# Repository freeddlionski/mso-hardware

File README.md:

# МСО74 — железо

Плата контроллера, корпус поста и документация отладочной платы. Прошивка — `mso-firmware`, сервер — `mso-server`,
ферма — `mso-farm`. Сюда можно давать доступ разводчикам и конструкторам без доступа к коду.

| Папка | Что там |
|---|---|
| `plata/` | своя плата контроллера: ТЗ для разработчиков (`TZ_razrabotchiku.md`) и рабочий черновик (`TZ.md`), дальше — схема, разводка, Gerber и BOM по ревизиям (`rev_A/`, `rev_B/`…) |
| `korpus/` | корпус поста: эскизы модулей, чертежи и файлы резки (`chertezhi/modul_tablo/` — модуль табло, в работе) |
| `a147/` | документация отладочной платы A147 (стенд): схемы производителя |

Как подключается периферия к контроллеру и что делает прошивка (MDB, монетник) — `mso-firmware/docs/MDB.md`.

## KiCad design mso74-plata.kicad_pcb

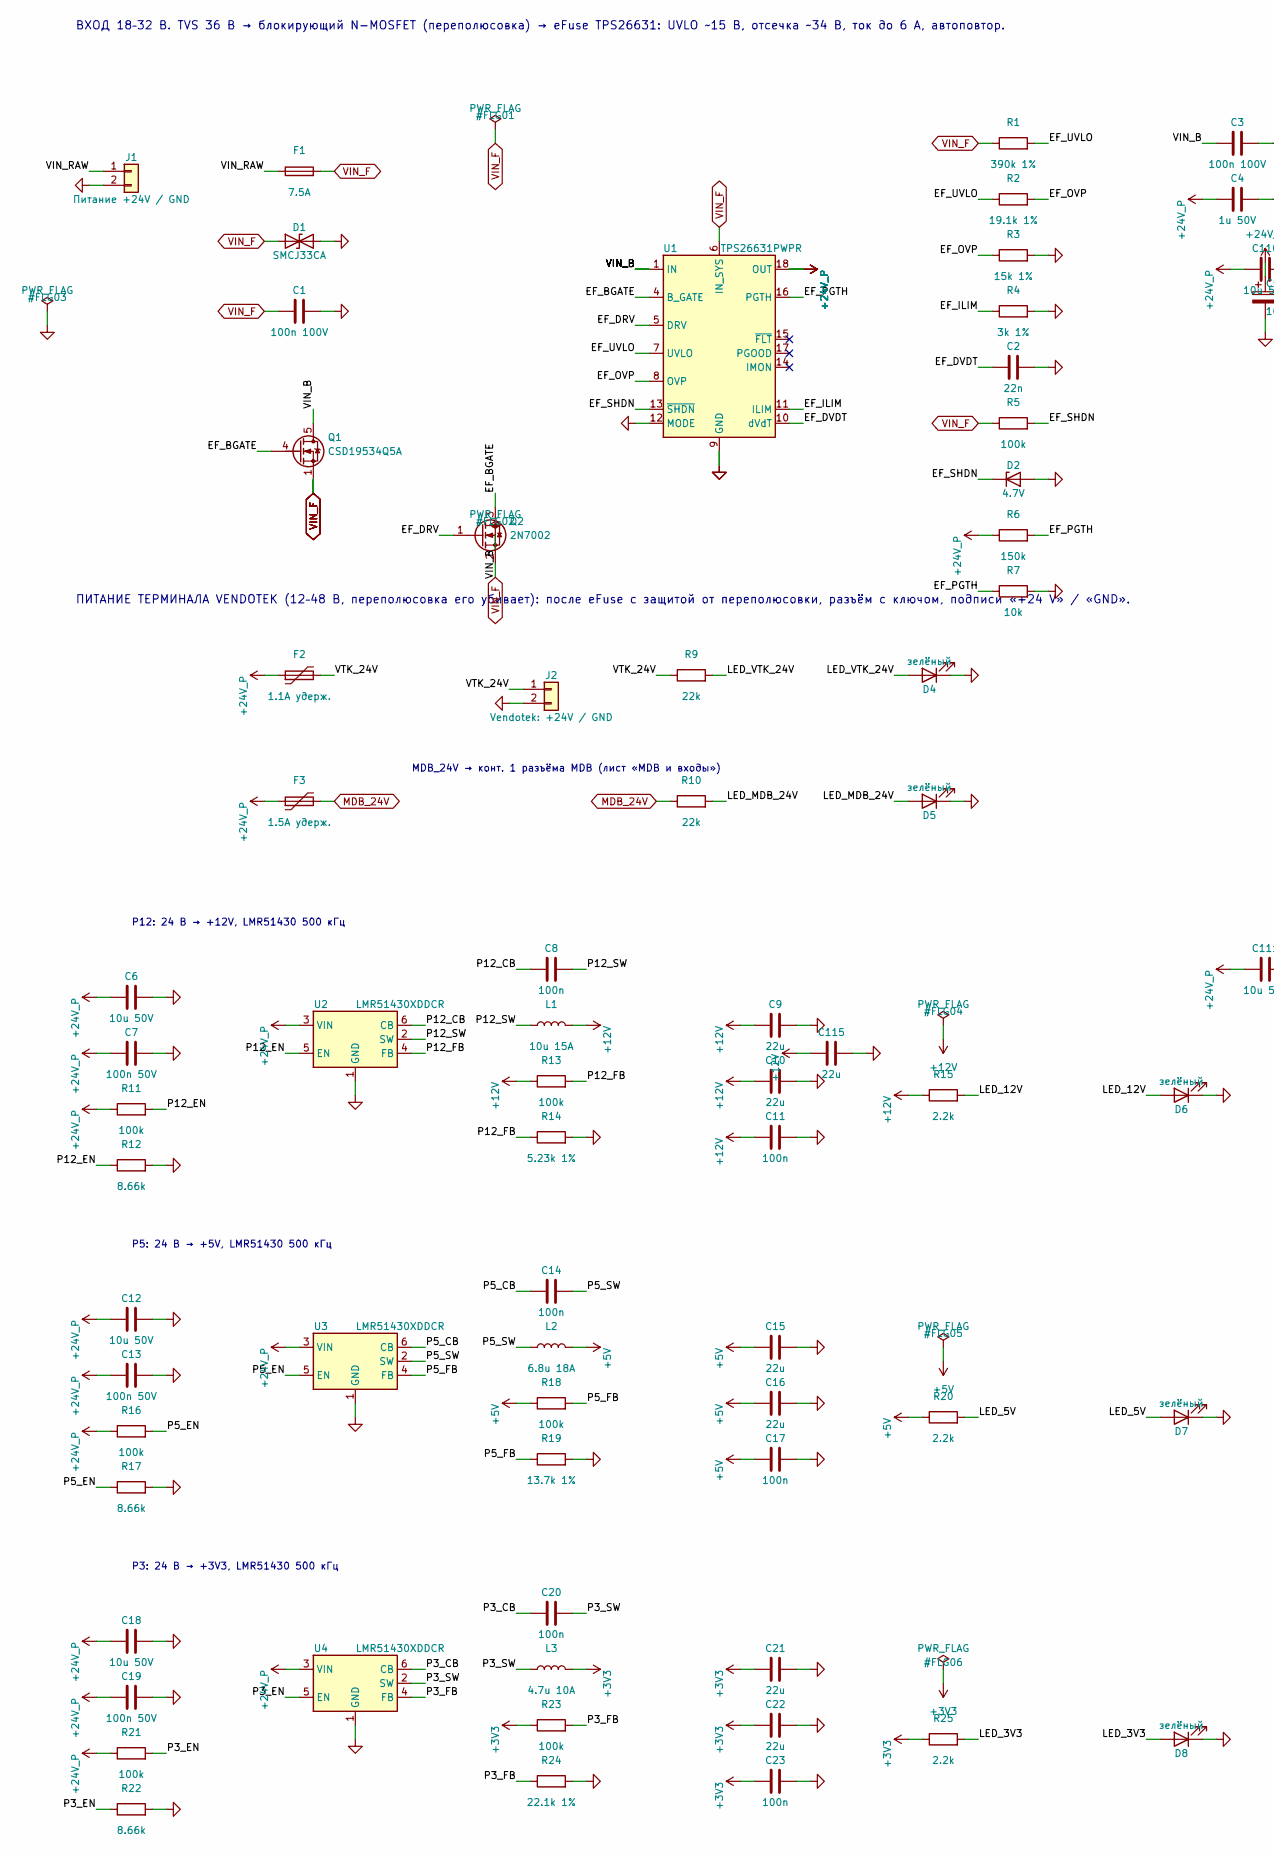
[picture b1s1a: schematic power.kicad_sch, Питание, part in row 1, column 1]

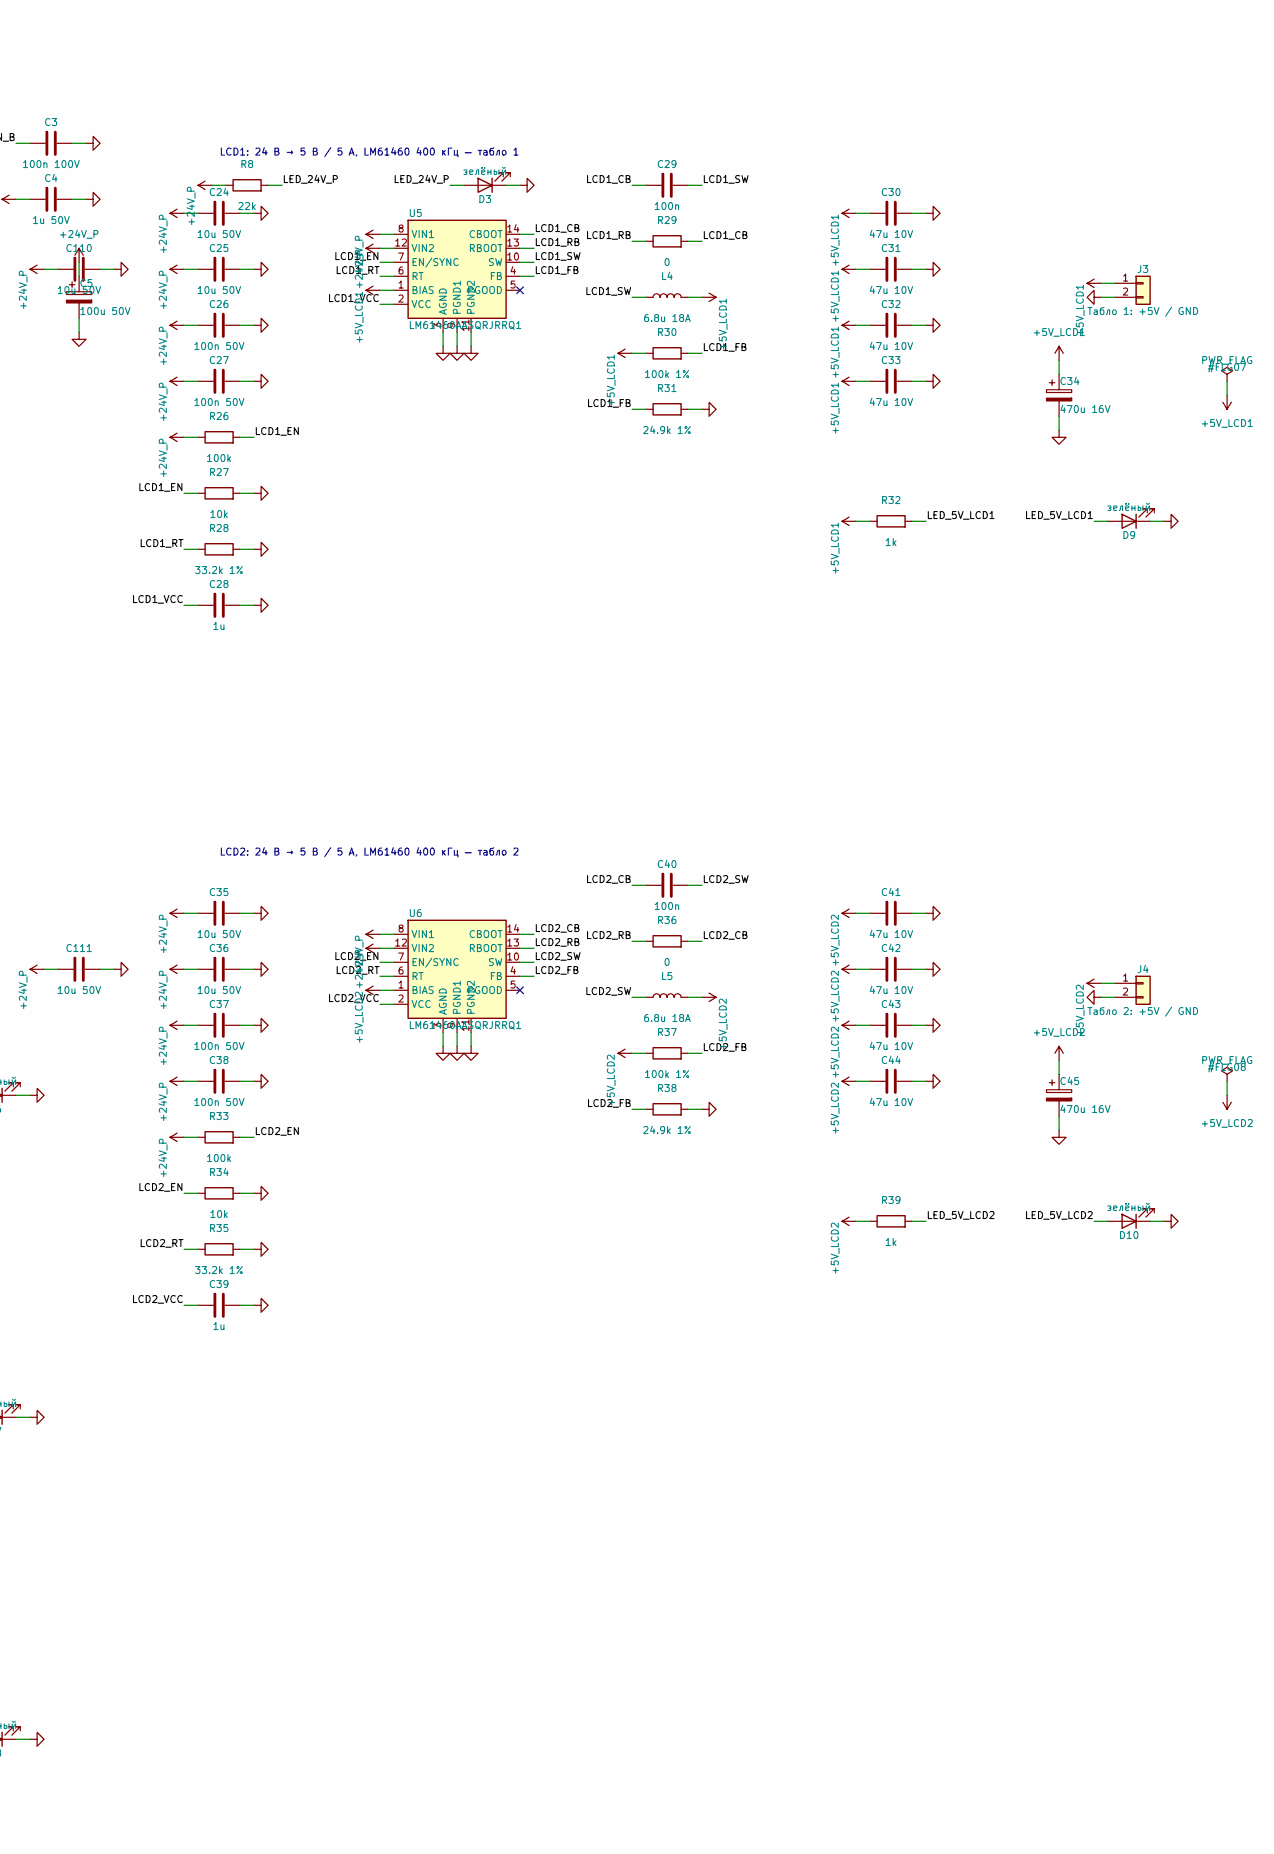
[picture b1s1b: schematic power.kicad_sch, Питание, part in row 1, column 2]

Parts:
C1, C3: 100n 100V; C_0603_1608Metric; MPN CL10B104KC8NNNC; LCSC C15725
C2: 22n; C_0603_1608Metric; MPN CC0603JRX7R9BB223; LCSC C277528
C4: 1u 50V; C_1206_3216Metric; MPN CL31B105KBHNNNE; LCSC C1848
C5: 100u 50V; CP_Elec_10x10.5; MPN MAL214699103E3; LCSC C5158069
C6, C12, C18, C24, C25, C35, C36, C110, C111: 10u 50V; C_1210_3225Metric; MPN GRM32ER71H106KA12L; LCSC C77102
C7, C13, C19, C26, C27, C37, C38: 100n 50V; C_0603_1608Metric; MPN CC0603KRX7R9BB104; LCSC C14663
C8, C11, C14, C17, C20, C23, C29, C40: 100n; C_0603_1608Metric; MPN CC0603KRX7R9BB104; LCSC C14663
C9, C10, C115: 22u; C_1210_3225Metric; MPN CL32A226KAJNNNE; LCSC C52306
C15, C16, C21, C22: 22u; C_1206_3216Metric; MPN CL31A226KOHNNNE; LCSC C90146
C28, C39: 1u; C_0603_1608Metric; MPN 0603X105K500NT; LCSC C157684
C30, C31, C32, C33, C41, C42, C43, C44: 47u 10V; C_1210_3225Metric; MPN C3225X5R1A476MT000E; LCSC C76680
C34, C45: 470u 16V; CP_Elec_10x10.5; MPN 25TLV470M10X10.5; LCSC C2905295
D1: SMCJ33CA; D_SMC; MPN SMCJ33CA; LCSC C224050
D2: 4.7V; D_SOD-123; MPN MMSZ4688; LCSC C22395547
D3, D4, D5, D6, D7, D8, D9, D10: зелёный; LED_0603_1608Metric; MPN KT-0603YG; LCSC C2289
F1: 7.5A; Fuseholder_Blade_Mini_Keystone_3568; MPN 3568-10; LCSC C3205378
F2: 1.1A удерж.; Fuse_2920_7451Metric; MPN 2920L110/60MR; LCSC C315903
F3: 1.5A удерж.; Fuse_2920_7451Metric; MPN SMD2920-150/60N; LCSC C6165178
J1: Питание +24V / GND; KANGNEX_WJ2EDGRC_1x02_P5.08mm_Drill1.7; MPN WJ2EDGRC-5.08-02P-14-00A; LCSC C3697
J2: Vendotek: +24V / GND; KANGNEX_WJ2EDGRC_1x02_P5.08mm_Drill1.7; MPN WJ2EDGRC-5.08-02P-14-00A; LCSC C3697
J3: Табло 1: +5V / GND; TerminalBlock_Phoenix_MKDS-1,5-2-5.08_1x02_P5.08mm_Horizont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; MPN WJ500V-5.08-2P; LCSC C8465
J4: Табло 2: +5V / GND; TerminalBlock_Phoenix_MKDS-1,5-2-5.08_1x02_P5.08mm_Horizont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; MPN WJ500V-5.08-2P; LCSC C8465
L1: 10u 15A; L_Bourns_SRP1245A; MPN SRP1265A-100M; LCSC C840531
L2, L4, L5: 6.8u 18A; L_Bourns_SRP1245A; MPN SRP1265A-6R8M; LCSC C2041326
L3: 4.7u 10A; L_Bourns_SRP7028A_7.3x6.6mm; MPN SRP7028A-4R7M; LCSC C840529
Q1: CSD19534Q5A; Texas_DQJ_VSONP-8_5x6mm_CSD19534Q5A; MPN CSD19534Q5A; LCSC C114200
Q2: 2N7002; SOT-23; MPN 2N7002-7-F (Diodes Inc.); LCSC C85049
R1: 390k 1%; R_0603_1608Metric; MPN 0603WAF3903T5E; LCSC C23150
R2: 19.1k 1%; R_0603_1608Metric; MPN 0603WAF1912T5E; LCSC C22897
R3: 15k 1%; R_0603_1608Metric; MPN 0603WAF1502T5E; LCSC C22809
R4: 3k 1%; R_0603_1608Metric; MPN 0603WAF3001T5E; LCSC C4211
R5, R11, R13, R16, R18, R21, R23, R26, R33: 100k; R_0603_1608Metric; MPN 0603WAF1003T5E; LCSC C25803
R6: 150k; R_0603_1608Metric; MPN 0603WAF1503T5E; LCSC C22807
R7, R27, R34: 10k; R_0603_1608Metric; MPN 0603WAF1002T5E; LCSC C25804
R8, R9, R10: 22k; R_0603_1608Metric; MPN 0603WAF2202T5E; LCSC C31850
R12, R17, R22: 8.66k; R_0603_1608Metric; MPN 0603WAF8661T5E; LCSC C23114
R14: 5.23k 1%; R_0603_1608Metric; MPN 0603WAF5231T5E; LCSC C23068
R15, R20, R25: 2.2k; R_0603_1608Metric; MPN 0603WAF2201T5E; LCSC C4190
R19: 13.7k 1%; R_0603_1608Metric; MPN 0603WAF1372T5E; LCSC C22793
R24: 22.1k 1%; R_0603_1608Metric; MPN FRC0603F2212TS; LCSC C2960862
R28, R35: 33.2k 1%; R_0603_1608Metric; MPN RC0603FR-0733K2L; LCSC C185338
R29, R36: 0; R_0603_1608Metric; MPN 0603WAF0000T5E; LCSC C21189
R30, R37: 100k 1%; R_0603_1608Metric; MPN 0603WAF1003T5E; LCSC C25803
R31, R38: 24.9k 1%; R_0603_1608Metric; MPN RC0603FR-0724K9L; LCSC C137761
R32, R39: 1k; R_0603_1608Metric; MPN 0603WAF1001T5E; LCSC C21190
U1: TPS26631PWPR; HTSSOP-20-1EP_4.4x6.5mm_P0.65mm_EP3.4x6.5mm_Mask2.96x2.96mm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; MPN TPS26631PWPR; LCSC C2866319
U2, U3, U4: LMR51430XDDCR; SOT-23-6; MPN LMR51430XDDCR; LCSC C5185863
U5, U6: LM61460AASQRJRRQ1; Texas_RJR_VQFN-HR-14_3.5x4mm; MPN LM61460AASQRJRRQ1; LCSC C1855832

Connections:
+3V3: C21.1, C22.1, C23.1, L3.2, R23.1, R25.1; also elsewhere on the board
+5V: C15.1, C16.1, C17.1, L2.2, R18.1, R20.1; also elsewhere on the board
+5V_LCD1: C30.1, C31.1, C32.1, C33.1, C34.1, J3.1, L4.2, R30.1, R32.1, U5.1 (BIAS); also elsewhere on the board
+5V_LCD2: C41.1, C42.1, C43.1, C44.1, C45.1, J4.1, L5.2, R37.1, R39.1, U6.1 (BIAS); also elsewhere on the board
+12V: C9.1, C10.1, C11.1, C115.1, L1.2, R13.1, R15.1; also elsewhere on the board
+24V_P: C4.1, C5.1, C6.1, C7.1, C12.1, C13.1, C18.1, C19.1, C24.1, C25.1, C26.1, C27.1, C35.1, C36.1, C37.1, C38.1, C110.1, C111.1, F2.1, F3.1, R6.1, R8.1, R11.1, R16.1, R21.1, R26.1, R33.1, U1.18 (OUT), U1.19 (OUT), U1.20 (OUT), U2.3 (VIN), U3.3 (VIN), U4.3 (VIN), U5.8 (VIN1), U5.12 (VIN2), U6.8 (VIN1), U6.12 (VIN2); also elsewhere on the board
/Питание/EF_BGATE: Q1.4 (G), Q2.3 (D), U1.4 (B_GATE)
/Питание/EF_DRV: Q2.1 (G), U1.5 (DRV)
/Питание/EF_DVDT: C2.1, U1.10 (dVdT)
/Питание/EF_ILIM: R4.1, U1.11 (ILIM)
/Питание/EF_OVP: R2.2, R3.1, U1.8 (OVP)
/Питание/EF_PGTH: R6.2, R7.1, U1.16 (PGTH)
/Питание/EF_SHDN: D2.1 (K), R5.2, U1.13 (~SHDN)
/Питание/EF_UVLO: R1.2, R2.1, U1.7 (UVLO)
/Питание/LCD1_CB: C29.1, R29.2, U5.14 (CBOOT)
/Питание/LCD1_EN: R26.2, R27.1, U5.7 (EN/SYNC)
/Питание/LCD1_FB: R30.2, R31.1, U5.4 (FB)
/Питание/LCD1_RB: R29.1, U5.13 (RBOOT)
/Питание/LCD1_RT: R28.1, U5.6 (RT)
/Питание/LCD1_SW: C29.2, L4.1, U5.10 (SW)
/Питание/LCD1_VCC: C28.1, U5.2 (VCC)
/Питание/LCD2_CB: C40.1, R36.2, U6.14 (CBOOT)
/Питание/LCD2_EN: R33.2, R34.1, U6.7 (EN/SYNC)
/Питание/LCD2_FB: R37.2, R38.1, U6.4 (FB)
/Питание/LCD2_RB: R36.1, U6.13 (RBOOT)
/Питание/LCD2_RT: R35.1, U6.6 (RT)
/Питание/LCD2_SW: C40.2, L5.1, U6.10 (SW)
/Питание/LCD2_VCC: C39.1, U6.2 (VCC)
/Питание/LED_3V3: D8.2 (A), R25.2
/Питание/LED_5V: D7.2 (A), R20.2
/Питание/LED_5V_LCD1: D9.2 (A), R32.2
/Питание/LED_5V_LCD2: D10.2 (A), R39.2
/Питание/LED_12V: D6.2 (A), R15.2
/Питание/LED_24V_P: D3.2 (A), R8.2
/Питание/LED_MDB_24V: D5.2 (A), R10.2
/Питание/LED_VTK_24V: D4.2 (A), R9.2
/Питание/P3_CB: C20.1, U4.6 (CB)
/Питание/P3_EN: R21.2, R22.1, U4.5 (EN)
/Питание/P3_FB: R23.2, R24.1, U4.4 (FB)
/Питание/P3_SW: C20.2, L3.1, U4.2 (SW)
/Питание/P5_CB: C14.1, U3.6 (CB)
/Питание/P5_EN: R16.2, R17.1, U3.5 (EN)
/Питание/P5_FB: R18.2, R19.1, U3.4 (FB)
/Питание/P5_SW: C14.2, L2.1, U3.2 (SW)
/Питание/P12_CB: C8.1, U2.6 (CB)
/Питание/P12_EN: R11.2, R12.1, U2.5 (EN)
/Питание/P12_FB: R13.2, R14.1, U2.4 (FB)
/Питание/P12_SW: C8.2, L1.1, U2.2 (SW)
/Питание/VIN_B: C3.1, Q1.5 (D), U1.1 (IN), U1.2 (IN), U1.3 (IN)
/Питание/VIN_RAW: F1.1, J1.1
/Питание/VTK_24V: F2.2, J2.1, R9.1
GND: C1.2, C2.2, C3.2, C4.2, C5.2, C6.2, C7.2, C9.2, C10.2, C11.2, C12.2, C13.2, C15.2, C16.2, C17.2, C18.2, C19.2, C21.2, C22.2, C23.2, C24.2, C25.2, C26.2, C27.2, C28.2, C30.2, C31.2, C32.2, C33.2, C34.2, C35.2, C36.2, C37.2, C38.2, C39.2, C41.2, C42.2, C43.2, C44.2, C45.2, C110.2, C111.2, C115.2, D1.2 (A2), D2.2 (A), D3.1 (K), D4.1 (K), D5.1 (K), D6.1 (K), D7.1 (K), D8.1 (K), D9.1 (K), D10.1 (K), J1.2, J2.2, J3.2, J4.2, R3.2, R4.2, R7.2, R12.2, R14.2, R17.2, R19.2, R22.2, R24.2, R27.2, R28.2, R31.2, R34.2, R35.2, R38.2, U1.9 (GND), U1.12 (MODE), U1.21 (GND), U2.1 (GND), U3.1 (GND), U4.1 (GND), U5.3 (AGND), U5.9 (PGND1), U5.11 (PGND2), U6.3 (AGND), U6.9 (PGND1), U6.11 (PGND2); also elsewhere on the board
MDB_24V: F3.2, R10.1; also elsewhere on the board
VIN_F: C1.1, D1.1 (A1), F1.2, Q1.1 (S), Q1.2 (S), Q1.3 (S), Q2.2 (S), R1.1, R5.1, U1.6 (IN_SYS); also elsewhere on the board

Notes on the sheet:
ВХОД 18–32 В. TVS 36 В → блокирующий N-MOSFET (переполюсовка) → eFuse TPS26631: UVLO ~15 В, отсечка ~34 В, ток до 6 А, автоповтор.
ПИТАНИЕ ТЕРМИНАЛА VENDOTEK (12–48 В, переполюсовка его убивает): после eFuse с защитой от переполюсовки, разъём с ключом, подписи «+24 V» / «GND».
MDB_24V → конт. 1 разъёма MDB (лист «MDB и входы»)
P12: 24 В → +12V, LMR51430 500 кГц
P5: 24 В → +5V, LMR51430 500 кГц
P3: 24 В → +3V3, LMR51430 500 кГц
LCD1: 24 В → 5 В / 5 А, LM61460 400 кГц — табло 1
LCD2: 24 В → 5 В / 5 А, LM61460 400 кГц — табло 2

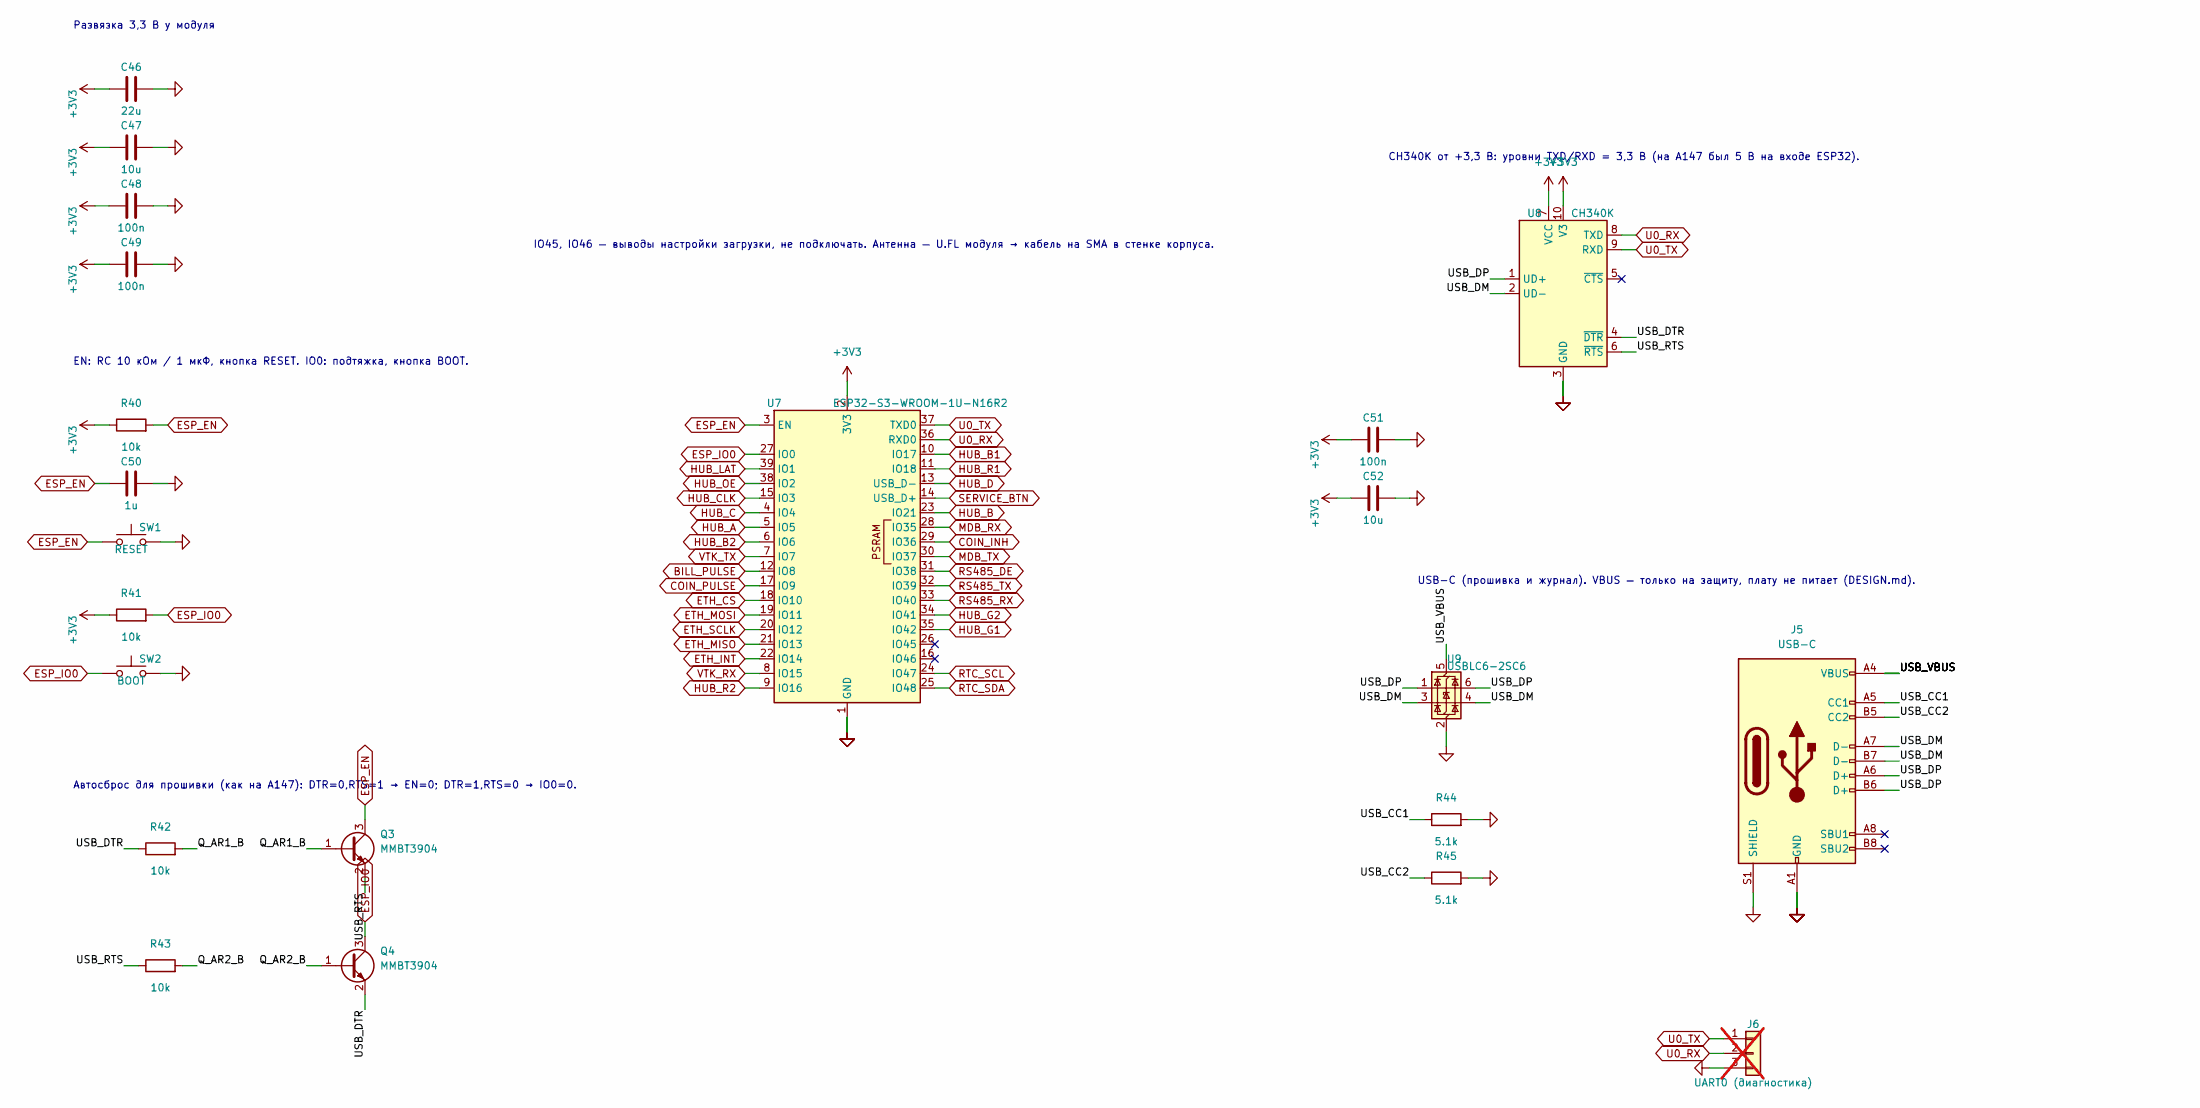
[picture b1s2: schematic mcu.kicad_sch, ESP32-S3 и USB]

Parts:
C46: 22u; C_1206_3216Metric; MPN CL31A226KOHNNNE; LCSC C90146
C47, C52: 10u; C_0805_2012Metric; MPN CL21A106KOQNNNE; LCSC C1713
C48, C49, C51: 100n; C_0603_1608Metric; MPN CC0603KRX7R9BB104; LCSC C14663
C50: 1u; C_0603_1608Metric; MPN 0603X105K500NT; LCSC C157684
J5: USB-C; USB_C_Receptacle_HCTL_HC-TYPE-C-16P-01A; MPN HC-TYPE-C-16P-01A; LCSC C2894897
J6: UART0 (диагностика); PinHeader_1x03_P2.54mm_Vertical; MPN 2.54-1*3P; LCSC C49257; not fitted
Q3, Q4: MMBT3904; SOT-23; MPN MMBT3904; LCSC C20526
R40, R41, R42, R43: 10k; R_0603_1608Metric; MPN 0603WAF1002T5E; LCSC C25804
R44, R45: 5.1k; R_0603_1608Metric; MPN 0603WAF5101T5E; LCSC C23186
SW1: RESET; SW_SPST_TL3342; MPN TL3342F450QG; LCSC C2886897
SW2: BOOT; SW_SPST_TL3342; MPN TL3342F450QG; LCSC C2886897
U7: ESP32-S3-WROOM-1U-N16R2; ESP32-S3-WROOM-1U; MPN ESP32-S3-WROOM-1U-N16R2; LCSC C3013945
U8: CH340K; SSOP-10-1EP_3.9x4.9mm_P1mm_EP2.1x3.3mm; MPN CH340K; LCSC C968586
U9: USBLC6-2SC6; SOT-23-6; MPN USBLC6-2SC6; LCSC C7519

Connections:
+3V3: C46.1, C47.1, C48.1, C49.1, C51.1, C52.1, R40.1, R41.1, U7.2 (3V3), U8.7 (VCC), U8.10 (V3); also elsewhere on the board
/ESP32-S3 и USB/Q_AR1_B: Q3.1 (B), R42.2
/ESP32-S3 и USB/Q_AR2_B: Q4.1 (B), R43.2
/ESP32-S3 и USB/USB_CC1: J5.A5 (CC1), R44.1
/ESP32-S3 и USB/USB_CC2: J5.B5 (CC2), R45.1
/ESP32-S3 и USB/USB_DM: J5.A7 (D-), J5.B7 (D-), U8.2 (UD-), U9.3 (I/O2), U9.4 (I/O2)
/ESP32-S3 и USB/USB_DP: J5.A6 (D+), J5.B6 (D+), U8.1 (UD+), U9.1 (I/O1), U9.6 (I/O1)
/ESP32-S3 и USB/USB_DTR: Q4.2 (E), R42.1, U8.4 (~DTR)
/ESP32-S3 и USB/USB_RTS: Q3.2 (E), R43.1, U8.6 (~RTS)
/ESP32-S3 и USB/USB_VBUS: J5.A4 (VBUS), J5.A9 (VBUS), J5.B4 (VBUS), J5.B9 (VBUS), U9.5 (VBUS)
BILL_PULSE: U7.12 (IO8); also elsewhere on the board
COIN_INH: U7.29 (IO36); also elsewhere on the board
COIN_PULSE: U7.17 (IO9); also elsewhere on the board
ESP_EN: C50.1, Q3.3 (C), R40.2, SW1.1, U7.3 (EN); also elsewhere on the board
ESP_IO0: Q4.3 (C), R41.2, SW2.1, U7.27 (IO0); also elsewhere on the board
ETH_CS: U7.18 (IO10); also elsewhere on the board
ETH_INT: U7.22 (IO14); also elsewhere on the board
ETH_MISO: U7.21 (IO13); also elsewhere on the board
ETH_MOSI: U7.19 (IO11); also elsewhere on the board
ETH_SCLK: U7.20 (IO12); also elsewhere on the board
GND: C46.2, C47.2, C48.2, C49.2, C50.2, C51.2, C52.2, J5.A1 (GND), J5.A12 (GND), J5.B1 (GND), J5.B12 (GND), J5.S1 (SHIELD), J6.3, R44.2, R45.2, SW1.2, SW2.2, U7.1 (GND), U7.40 (GND), U7.41 (GND), U8.3 (GND), U8.11 (GND), U9.2 (GND); also elsewhere on the board
HUB_A: U7.5 (IO5); also elsewhere on the board
HUB_B: U7.23 (IO21); also elsewhere on the board
HUB_B1: U7.10 (IO17); also elsewhere on the board
HUB_B2: U7.6 (IO6); also elsewhere on the board
HUB_C: U7.4 (IO4); also elsewhere on the board
HUB_CLK: U7.15 (IO3); also elsewhere on the board
HUB_D: U7.13 (USB_D-); also elsewhere on the board
HUB_G1: U7.35 (IO42); also elsewhere on the board
HUB_G2: U7.34 (IO41); also elsewhere on the board
HUB_LAT: U7.39 (IO1); also elsewhere on the board
HUB_OE: U7.38 (IO2); also elsewhere on the board
HUB_R1: U7.11 (IO18); also elsewhere on the board
HUB_R2: U7.9 (IO16); also elsewhere on the board
MDB_RX: U7.28 (IO35); also elsewhere on the board
MDB_TX: U7.30 (IO37); also elsewhere on the board
RS485_DE: U7.31 (IO38); also elsewhere on the board
RS485_RX: U7.33 (IO40); also elsewhere on the board
RS485_TX: U7.32 (IO39); also elsewhere on the board
RTC_SCL: U7.24 (IO47); also elsewhere on the board
RTC_SDA: U7.25 (IO48); also elsewhere on the board
SERVICE_BTN: U7.14 (USB_D+); also elsewhere on the board
U0_RX: J6.2, U7.36 (RXD0), U8.8 (TXD); also elsewhere on the board
U0_TX: J6.1, U7.37 (TXD0), U8.9 (RXD); also elsewhere on the board
VTK_RX: U7.8 (IO15); also elsewhere on the board
VTK_TX: U7.7 (IO7); also elsewhere on the board

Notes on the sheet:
IO45, IO46 — выводы настройки загрузки, не подключать. Антенна — U.FL модуля → кабель на SMA в стенке корпуса.
Развязка 3,3 В у модуля
EN: RC 10 кОм / 1 мкФ, кнопка RESET. IO0: подтяжка, кнопка BOOT.
Автосброс для прошивки (как на A147): DTR=0,RTS=1 → EN=0; DTR=1,RTS=0 → IO0=0.
CH340K от +3,3 В: уровни TXD/RXD = 3,3 В (на A147 был 5 В на входе ESP32).
USB-C (прошивка и журнал). VBUS — только на защиту, платy не питает (DESIGN.md).

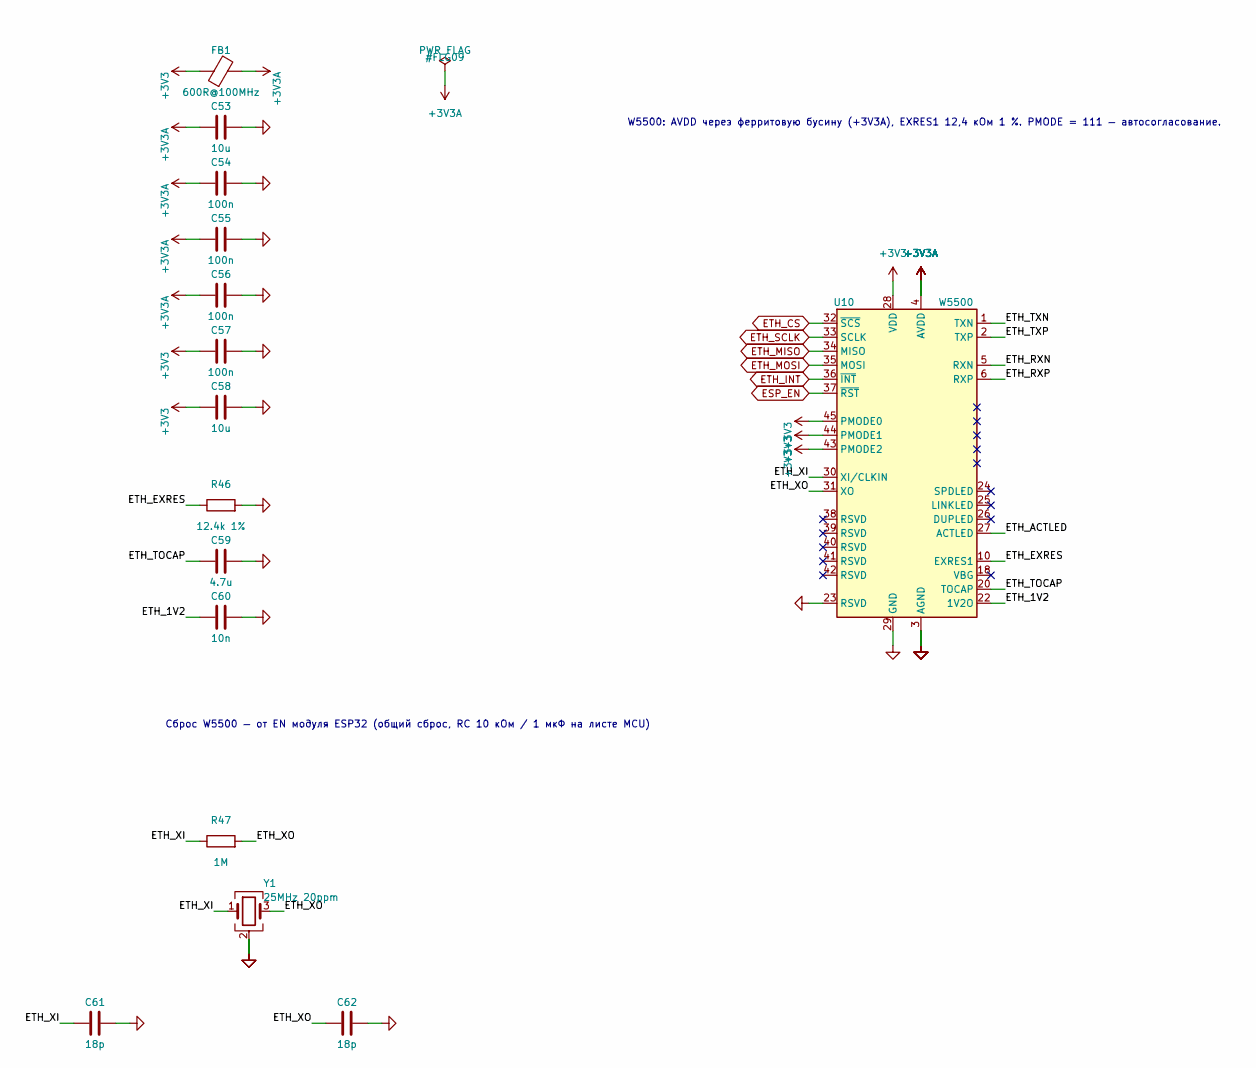
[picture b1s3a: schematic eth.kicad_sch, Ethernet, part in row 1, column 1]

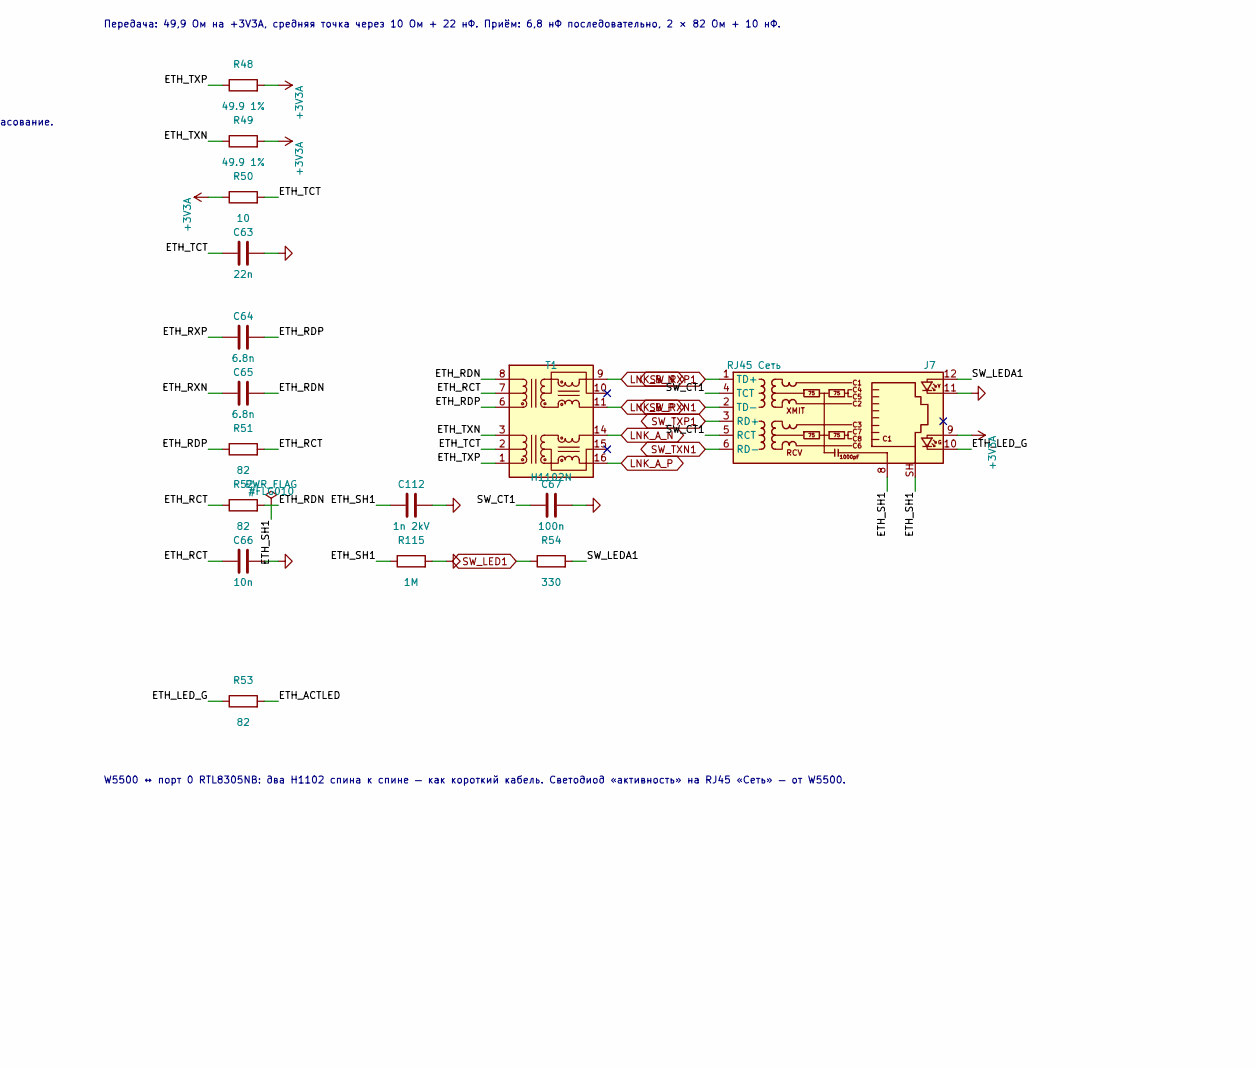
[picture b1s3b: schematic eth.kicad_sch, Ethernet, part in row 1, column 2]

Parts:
C53, C58: 10u; C_0805_2012Metric; MPN CL21A106KOQNNNE; LCSC C1713
C54, C55, C56, C57, C67: 100n; C_0603_1608Metric; MPN CC0603KRX7R9BB104; LCSC C14663
C59: 4.7u; C_0805_2012Metric; MPN CL21A475KAQNNNE; LCSC C1779
C60, C66: 10n; C_0603_1608Metric; MPN 0603B103K500NT; LCSC C57112
C61, C62: 18p; C_0603_1608Metric; MPN CL10C180JB8NNNC; LCSC C1647
C63: 22n; C_0603_1608Metric; MPN CC0603JRX7R9BB223; LCSC C277528
C64, C65: 6.8n; C_0603_1608Metric; MPN CC0603KRX7R9BB682; LCSC C107097
C112: 1n 2kV; C_1206_3216Metric; MPN 1206B102K202NT; LCSC C9196
FB1: 600R@100MHz; L_0805_2012Metric; LCSC C1017
J7: RJ45 Сеть; RJ45_Hanrun_HR911105A_Horizontal; MPN HR911105A; LCSC C12074
R46: 12.4k 1%; R_0603_1608Metric; MPN 0603WAF1242T5E; LCSC C22865
R47, R115: 1M; R_0603_1608Metric; MPN 0603WAF1004T5E; LCSC C22935
R48, R49: 49.9 1%; R_0603_1608Metric; MPN 0603WAF499JT5E; LCSC C23185
R50: 10; R_0603_1608Metric; MPN 0603WAF100JT5E; LCSC C22859
R51, R52, R53: 82; R_0603_1608Metric; MPN 0603WAF820JT5E; LCSC C23255
R54: 330; R_0603_1608Metric; MPN 0603WAF3300T5E; LCSC C23138
T1: H1102N; Transformer_Ethernet_CNDtek_H1102N; MPN CND-tek H1102N; LCSC C42418465
U10: W5500; LQFP-48_7x7mm_P0.5mm; MPN W5500; LCSC C32843
Y1: 25MHz 20ppm; Crystal_SMD_3225-4Pin_3.2x2.5mm; MPN X322525MOB4SI; LCSC C9006

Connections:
+3V3: C57.1, C58.1, FB1.1, U10.28 (VDD), U10.43 (PMODE2), U10.44 (PMODE1), U10.45 (PMODE0); also elsewhere on the board
+3V3A: C53.1, C54.1, C55.1, C56.1, FB1.2, J7.9, R48.2, R49.2, R50.1, U10.4 (AVDD), U10.8 (AVDD), U10.11 (AVDD), U10.15 (AVDD), U10.17 (AVDD), U10.21 (AVDD)
/Ethernet/ETH_1V2: C60.1, U10.22 (1V2O)
/Ethernet/ETH_ACTLED: R53.2, U10.27 (ACTLED)
/Ethernet/ETH_EXRES: R46.1, U10.10 (EXRES1)
/Ethernet/ETH_LED_G: J7.10, R53.1
/Ethernet/ETH_RCT: C66.1, R51.2, R52.1, T1.7 (C_RD)
/Ethernet/ETH_RDN: C65.2, R52.2, T1.8 (RD-)
/Ethernet/ETH_RDP: C64.2, R51.1, T1.6 (RD+)
/Ethernet/ETH_RXN: C65.1, U10.5 (RXN)
/Ethernet/ETH_RXP: C64.1, U10.6 (RXP)
/Ethernet/ETH_SH1: C112.1, J7.8, J7.SH, R115.1
/Ethernet/ETH_TCT: C63.1, R50.2, T1.2 (C_TD)
/Ethernet/ETH_TOCAP: C59.1, U10.20 (TOCAP)
/Ethernet/ETH_TXN: R49.1, T1.3 (TD-), U10.1 (TXN)
/Ethernet/ETH_TXP: R48.1, T1.1 (TD+), U10.2 (TXP)
/Ethernet/ETH_XI: C61.1, R47.1, U10.30 (XI/CLKIN), Y1.1
/Ethernet/ETH_XO: C62.1, R47.2, U10.31 (XO), Y1.3
/Ethernet/SW_CT1: C67.1, J7.4 (TCT), J7.5 (RCT)
/Ethernet/SW_LEDA1: J7.12, R54.2
ESP_EN: U10.37 (~RST); also elsewhere on the board
ETH_CS: U10.32 (~SCS); also elsewhere on the board
ETH_INT: U10.36 (~INT); also elsewhere on the board
ETH_MISO: U10.34 (MISO); also elsewhere on the board
ETH_MOSI: U10.35 (MOSI); also elsewhere on the board
ETH_SCLK: U10.33 (SCLK); also elsewhere on the board
GND: C53.2, C54.2, C55.2, C56.2, C57.2, C58.2, C59.2, C60.2, C61.2, C62.2, C63.2, C66.2, C67.2, C112.2, J7.11, R46.2, R115.2, U10.3 (AGND), U10.9 (AGND), U10.14 (AGND), U10.16 (AGND), U10.19 (AGND), U10.23 (RSVD), U10.29 (GND), U10.48 (AGND), Y1.2 (G), Y1.4 (G); also elsewhere on the board
LNK_A_N: T1.14 (TX-); also elsewhere on the board
LNK_A_P: T1.16 (TX+); also elsewhere on the board
LNK_B_N: T1.9 (RX-); also elsewhere on the board
LNK_B_P: T1.11 (RX+); also elsewhere on the board
SW_LED1: R54.1; also elsewhere on the board
SW_RXN1: J7.2 (TD-); also elsewhere on the board
SW_RXP1: J7.1 (TD+); also elsewhere on the board
SW_TXN1: J7.6 (RD-); also elsewhere on the board
SW_TXP1: J7.3 (RD+); also elsewhere on the board

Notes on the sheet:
W5500: AVDD через ферритовую бусину (+3V3A), EXRES1 12,4 кОм 1 %. PMODE = 111 — автосогласование.
Сброс W5500 — от EN модуля ESP32 (общий сброс, RC 10 кОм / 1 мкФ на листе MCU)
Передача: 49,9 Ом на +3V3A, средняя точка через 10 Ом + 22 нФ. Приём: 6,8 нФ последовательно, 2 × 82 Ом + 10 нФ.
W5500 ↔ порт 0 RTL8305NB: два H1102 спина к спине — как короткий кабель. Светодиод «активность» на RJ45 «Сеть» — от W5500.
